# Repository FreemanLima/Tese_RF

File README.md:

Repo para manter coerente a organização dos ficheiros

Por agora a ideia é implementar e validar um transciever em PCB low cost para justificar fazer um mais xpto

Começando pela familia C1 da Texas

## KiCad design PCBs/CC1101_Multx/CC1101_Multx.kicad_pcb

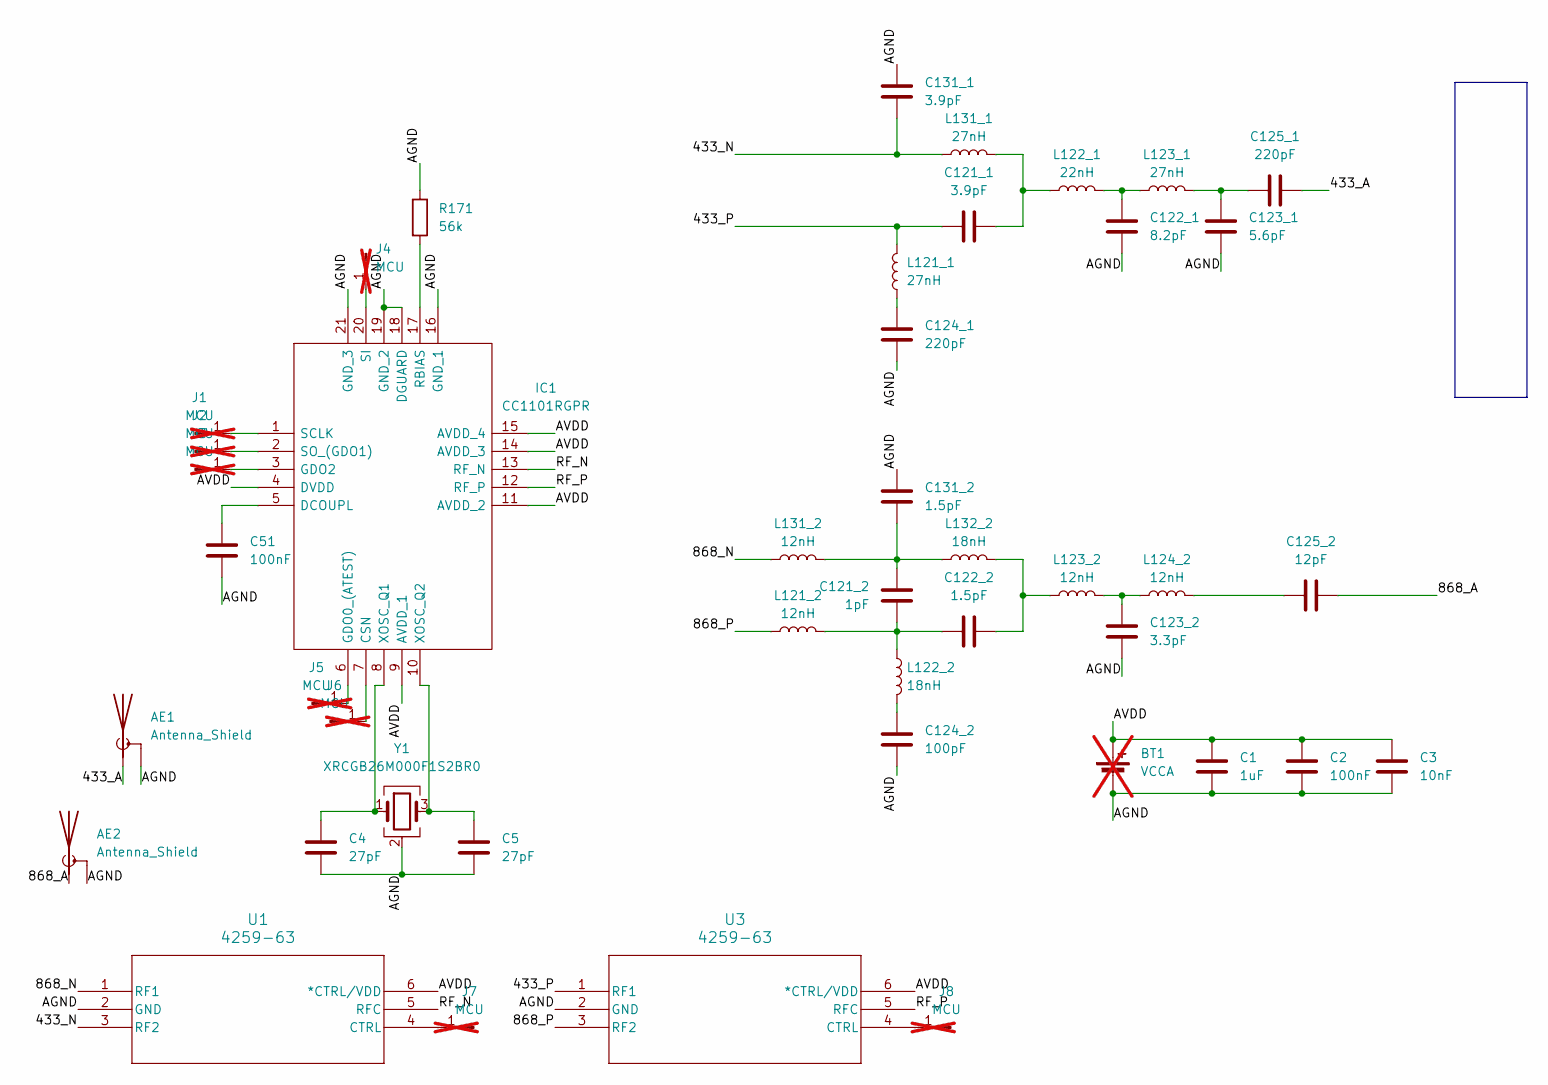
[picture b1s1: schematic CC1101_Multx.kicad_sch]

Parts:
AE1, AE2: Antenna_Shield; SMA_CONSMA020_062_G; Part Name CONSMA020.062-G; LCSC Part # C22467594
BT1: VCCA; PinHeader_1x02_P2.54mm_Vertical; not fitted
C1: 1uF; C_0603_1608Metric_Pad1.08x0.95mm_HandSolder; Part Name GRM155C71A105KE11J; LCSC Part # C126521
C2, C51: 100nF; C_0603_1608Metric_Pad1.08x0.95mm_HandSolder; Part Name GRM155C71H104JE19D; LCSC Part # C2189775
C3: 10nF; C_0603_1608Metric_Pad1.08x0.95mm_HandSolder; Part Name GRM155R71H103JA88D; LCSC Part # C162190
C4, C5: 27pF; C_0603_1608Metric_Pad1.08x0.95mm_HandSolder; Part Name GRM1555C1E270JA01D; LCSC Part # C710837
C121_1, C131_1: 3.9pF; C_0603_1608Metric_Pad1.08x0.95mm_HandSolder; Part Name GJM1555C1H3R9WB01D; LCSC Part # C88893
C121_2: 1pF; C_0603_1608Metric_Pad1.08x0.95mm_HandSolder; Part Name GCM1555C1H1R0JA16D; LCSC Part # C710646
C122_1: 8.2pF; C_0603_1608Metric_Pad1.08x0.95mm_HandSolder; Part Name GCQ1555C1H8R2WB01D; LCSC Part # C2272083
C122_2, C131_2: 1.5pF; C_0603_1608Metric_Pad1.08x0.95mm_HandSolder; Part Name GCM1555C1H1R5JA16D; LCSC Part # C710647
C123_1: 5.6pF; C_0603_1608Metric_Pad1.08x0.95mm_HandSolder; Part Name GJM1555C1H5R6BB01D; LCSC Part # C161329
C123_2: 3.3pF; C_0603_1608Metric_Pad1.08x0.95mm_HandSolder; Part Name GJM1555C1H3R3BB01D; LCSC Part # C76906
C124_1, C125_1: 220pF; C_0603_1608Metric_Pad1.08x0.95mm_HandSolder; Part Name GCM1555C1H221JA16D; LCSC Part # C126503
C124_2: 100pF; C_0603_1608Metric_Pad1.08x0.95mm_HandSolder; Part Name GCM1555C1H101FA16D; LCSC Part # C2941926
C125_2: 12pF; C_0603_1608Metric_Pad1.08x0.95mm_HandSolder; Part Name GRM1555C1H120JA01D; LCSC Part # C76948
IC1: CC1101RGPR; QFN50P400X400X100-21N-D; Mouser Part Number 595-CC1101RGPR
J1, J2, J3, J4, J5, J6, J7, J8: MCU; PinHeader_1x01_P2.54mm_Vertical; not fitted
L121_1, L123_1, L131_1: 27nH; L_0603_1608Metric; Part Name LQW15AN27NJ8ZD; LCSC Part # C2043861
L121_2, L123_2, L131_2: 12nH; L_0603_1608Metric; Part Name LQW15AN12NJ80D; LCSC Part # C2986278
L122_1: 22nH; L_0603_1608Metric; Part Name LQW15AN22NG8ZD; LCSC Part # C2044066
L122_2, L132_2: 18nH; L_0603_1608Metric; Part Name LQW15AN18NJ8ZD; LCSC Part # C437365
L124_2: 12nH; L_0603_1608Metric; Part Name LQW18AN12NG00D; LCSC Part # C98068
R171: 56k; R_0603_1608Metric_Pad0.98x0.95mm_HandSolder; Part Name ERJ-PA2F5602X; LCSC Part # C427251
U1, U3: 4259-63; SC-70-6_PSM-M; Part Name 4259-63; Digikey Part # 1046-1011-1-ND
Y1: XRCGB26M000F1S2BR0; Crystal_SMD_SeikoEpson_FA128-4Pin_2.0x1.6mm; Part Name XRCGB26M000F1S2BR0; LCSC Part # C7129840

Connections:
/433_A: AE1.1 (A), C125_1.1
/433_N: C131_1.1, L131_1.1, U1.3 (RF2)
/433_P: C121_1.1, L121_1.2, U3.1 (RF1)
/868_A: AE2.1 (A), C125_2.1
/868_N: L131_2.1, U1.1 (RF1)
/868_P: L121_2.1, U3.3 (RF2)
/AGND: AE1.2 (Shield), AE2.2 (Shield), BT1.2 (-), C1.1, C2.1, C3.1, C4.1, C5.1, C51.2, C122_1.1, C123_1.1, C123_2.1, C124_1.1, C124_2.1, C131_1.2, C131_2.2, IC1.16 (GND_1), IC1.18 (DGUARD), IC1.19 (GND_2), IC1.21 (GND_3), R171.1, U1.2 (GND), U3.2 (GND), Y1.2 (G), Y1.4 (G); also elsewhere on the board
/AVDD: BT1.1 (+), C1.2, C2.2, C3.2, IC1.4 (DVDD), IC1.9 (AVDD_1), IC1.11 (AVDD_2), IC1.14 (AVDD_3), IC1.15 (AVDD_4), U1.6 (*CTRL/VDD), U3.6 (*CTRL/VDD)
/RF_N: IC1.13 (RF_N), U1.5 (RFC)
/RF_P: IC1.12 (RF_P), U3.5 (RFC)
unnamed: C121_1.2, L122_1.1, L131_1.2
unnamed: C121_2.1, C131_2.1, L131_2.2, L132_2.1
unnamed: C121_2.2, C122_2.1, L121_2.2, L122_2.1
unnamed: C122_1.2, L122_1.2, L123_1.1
unnamed: C122_2.2, L123_2.1, L132_2.2
unnamed: C123_1.2, C125_1.2, L123_1.2
unnamed: C123_2.2, L123_2.2, L124_2.1
unnamed: C124_1.2, L121_1.1
unnamed: C124_2.2, L122_2.2
unnamed: C125_2.2, L124_2.2
unnamed: IC1.7 (CSN), J6.1 (Pin_1_1)
unnamed: C51.1, IC1.5 (DCOUPL)
unnamed: IC1.6 (GDO0_(ATEST)), J5.1 (Pin_1_1)
unnamed: IC1.3 (GDO2), J3.1 (Pin_1_1)
unnamed: IC1.17 (RBIAS), R171.2
unnamed: IC1.1 (SCLK), J1.1 (Pin_1_1)
unnamed: IC1.20 (SI), J4.1 (Pin_1_1)
unnamed: IC1.2 (SO_(GDO1)), J2.1 (Pin_1_1)
unnamed: C4.2, IC1.8 (XOSC_Q1), Y1.1
unnamed: C5.2, IC1.10 (XOSC_Q2), Y1.3
unnamed: J7.1 (Pin_1_1), U1.4 (CTRL)
unnamed: J8.1 (Pin_1_1), U3.4 (CTRL)

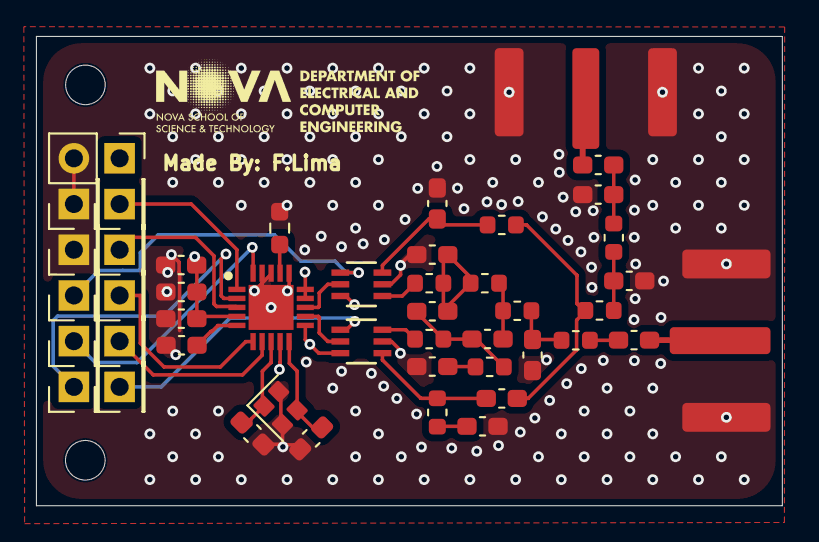
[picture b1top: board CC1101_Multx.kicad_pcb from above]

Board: 4 copper layers, 41.4 x 26.1 mm, 46 parts (0 on the bottom side), 32 nets.

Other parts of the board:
J1#2, J9: MCU; PinHeader_1x01_P2.54mm_Vertical

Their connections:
/AGND: J1#2.1 (Pin_1_1), J9.1 (Pin_1_1); also elsewhere on the board

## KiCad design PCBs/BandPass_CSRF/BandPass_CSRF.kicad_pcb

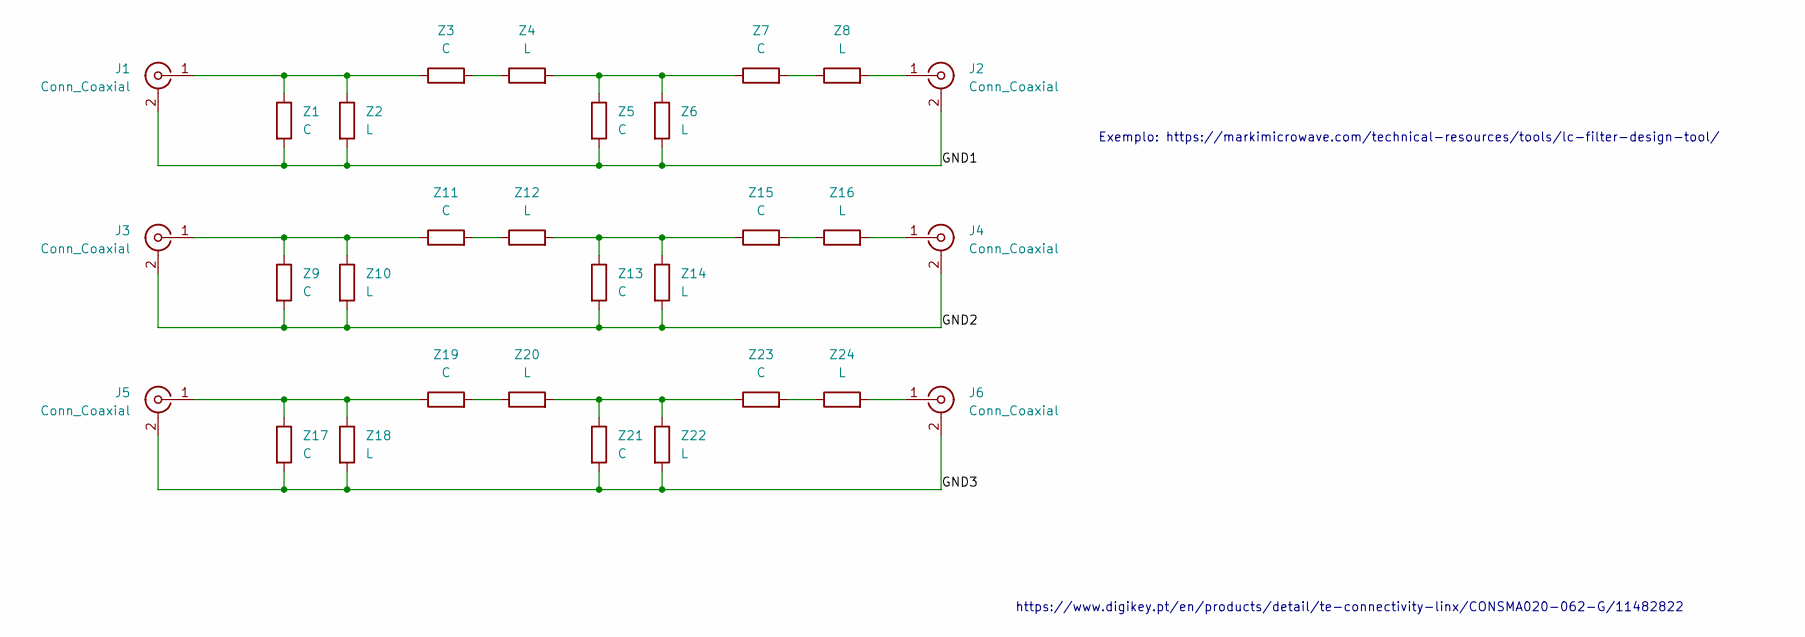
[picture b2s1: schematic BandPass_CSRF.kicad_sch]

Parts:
J1, J2, J3, J4, J5, J6: Conn_Coaxial; SMA_CONSMA020_062_G
Z1, Z3, Z5, Z7, Z9, Z11, Z13, Z15, Z17, Z19, Z21, Z23: C; C_0805_2012Metric_Pad1.18x1.45mm_HandSolder
Z2, Z4, Z6, Z8, Z10, Z12, Z14, Z16, Z18, Z20, Z22, Z24: L; C_0805_2012Metric_Pad1.18x1.45mm_HandSolder

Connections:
/GND1: J1.2 (Ext), J2.2 (Ext), Z1.2, Z2.2, Z5.2, Z6.2
/GND2: J3.2 (Ext), J4.2 (Ext), Z9.2, Z10.2, Z13.2, Z14.2
/GND3: J5.2 (Ext), J6.2 (Ext), Z17.2, Z18.2, Z21.2, Z22.2
unnamed: J1.1 (In), Z1.1, Z2.1, Z3.1
unnamed: J2.1 (In), Z8.2
unnamed: J3.1 (In), Z9.1, Z10.1, Z11.1
unnamed: J4.1 (In), Z16.2
unnamed: J5.1 (In), Z17.1, Z18.1, Z19.1
unnamed: J6.1 (In), Z24.2
unnamed: Z3.2, Z4.1
unnamed: Z4.2, Z5.1, Z6.1, Z7.1
unnamed: Z7.2, Z8.1
unnamed: Z11.2, Z12.1
unnamed: Z12.2, Z13.1, Z14.1, Z15.1
unnamed: Z15.2, Z16.1
unnamed: Z19.2, Z20.1
unnamed: Z20.2, Z21.1, Z22.1, Z23.1
unnamed: Z23.2, Z24.1

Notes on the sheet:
Exemplo: https://markimicrowave.com/technical-resources/tools/lc-filter-design-tool/
https://www.digikey.pt/en/products/detail/te-connectivity-linx/CONSMA020-062-G/11482822

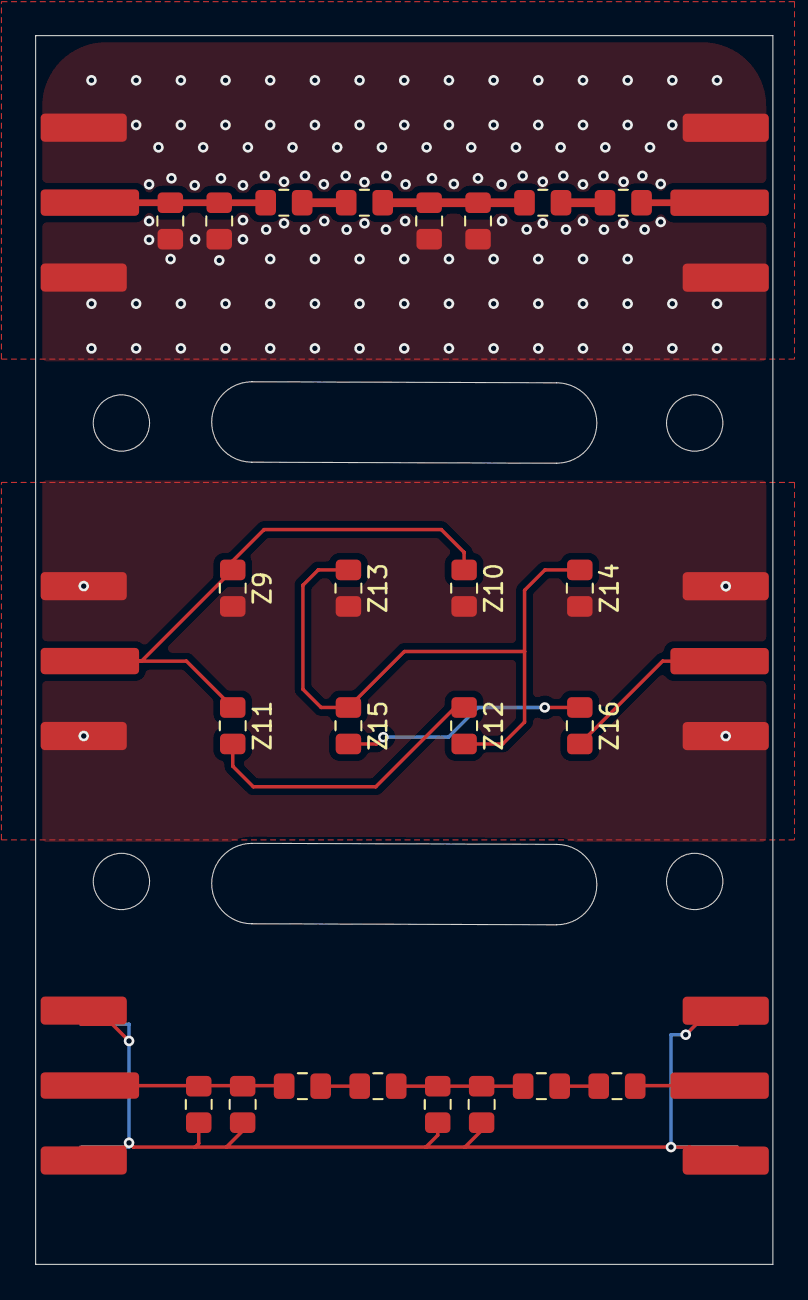
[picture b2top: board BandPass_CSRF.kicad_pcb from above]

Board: 2 copper layers, 41.9 x 69.9 mm, 30 parts (0 on the bottom side), 18 nets.

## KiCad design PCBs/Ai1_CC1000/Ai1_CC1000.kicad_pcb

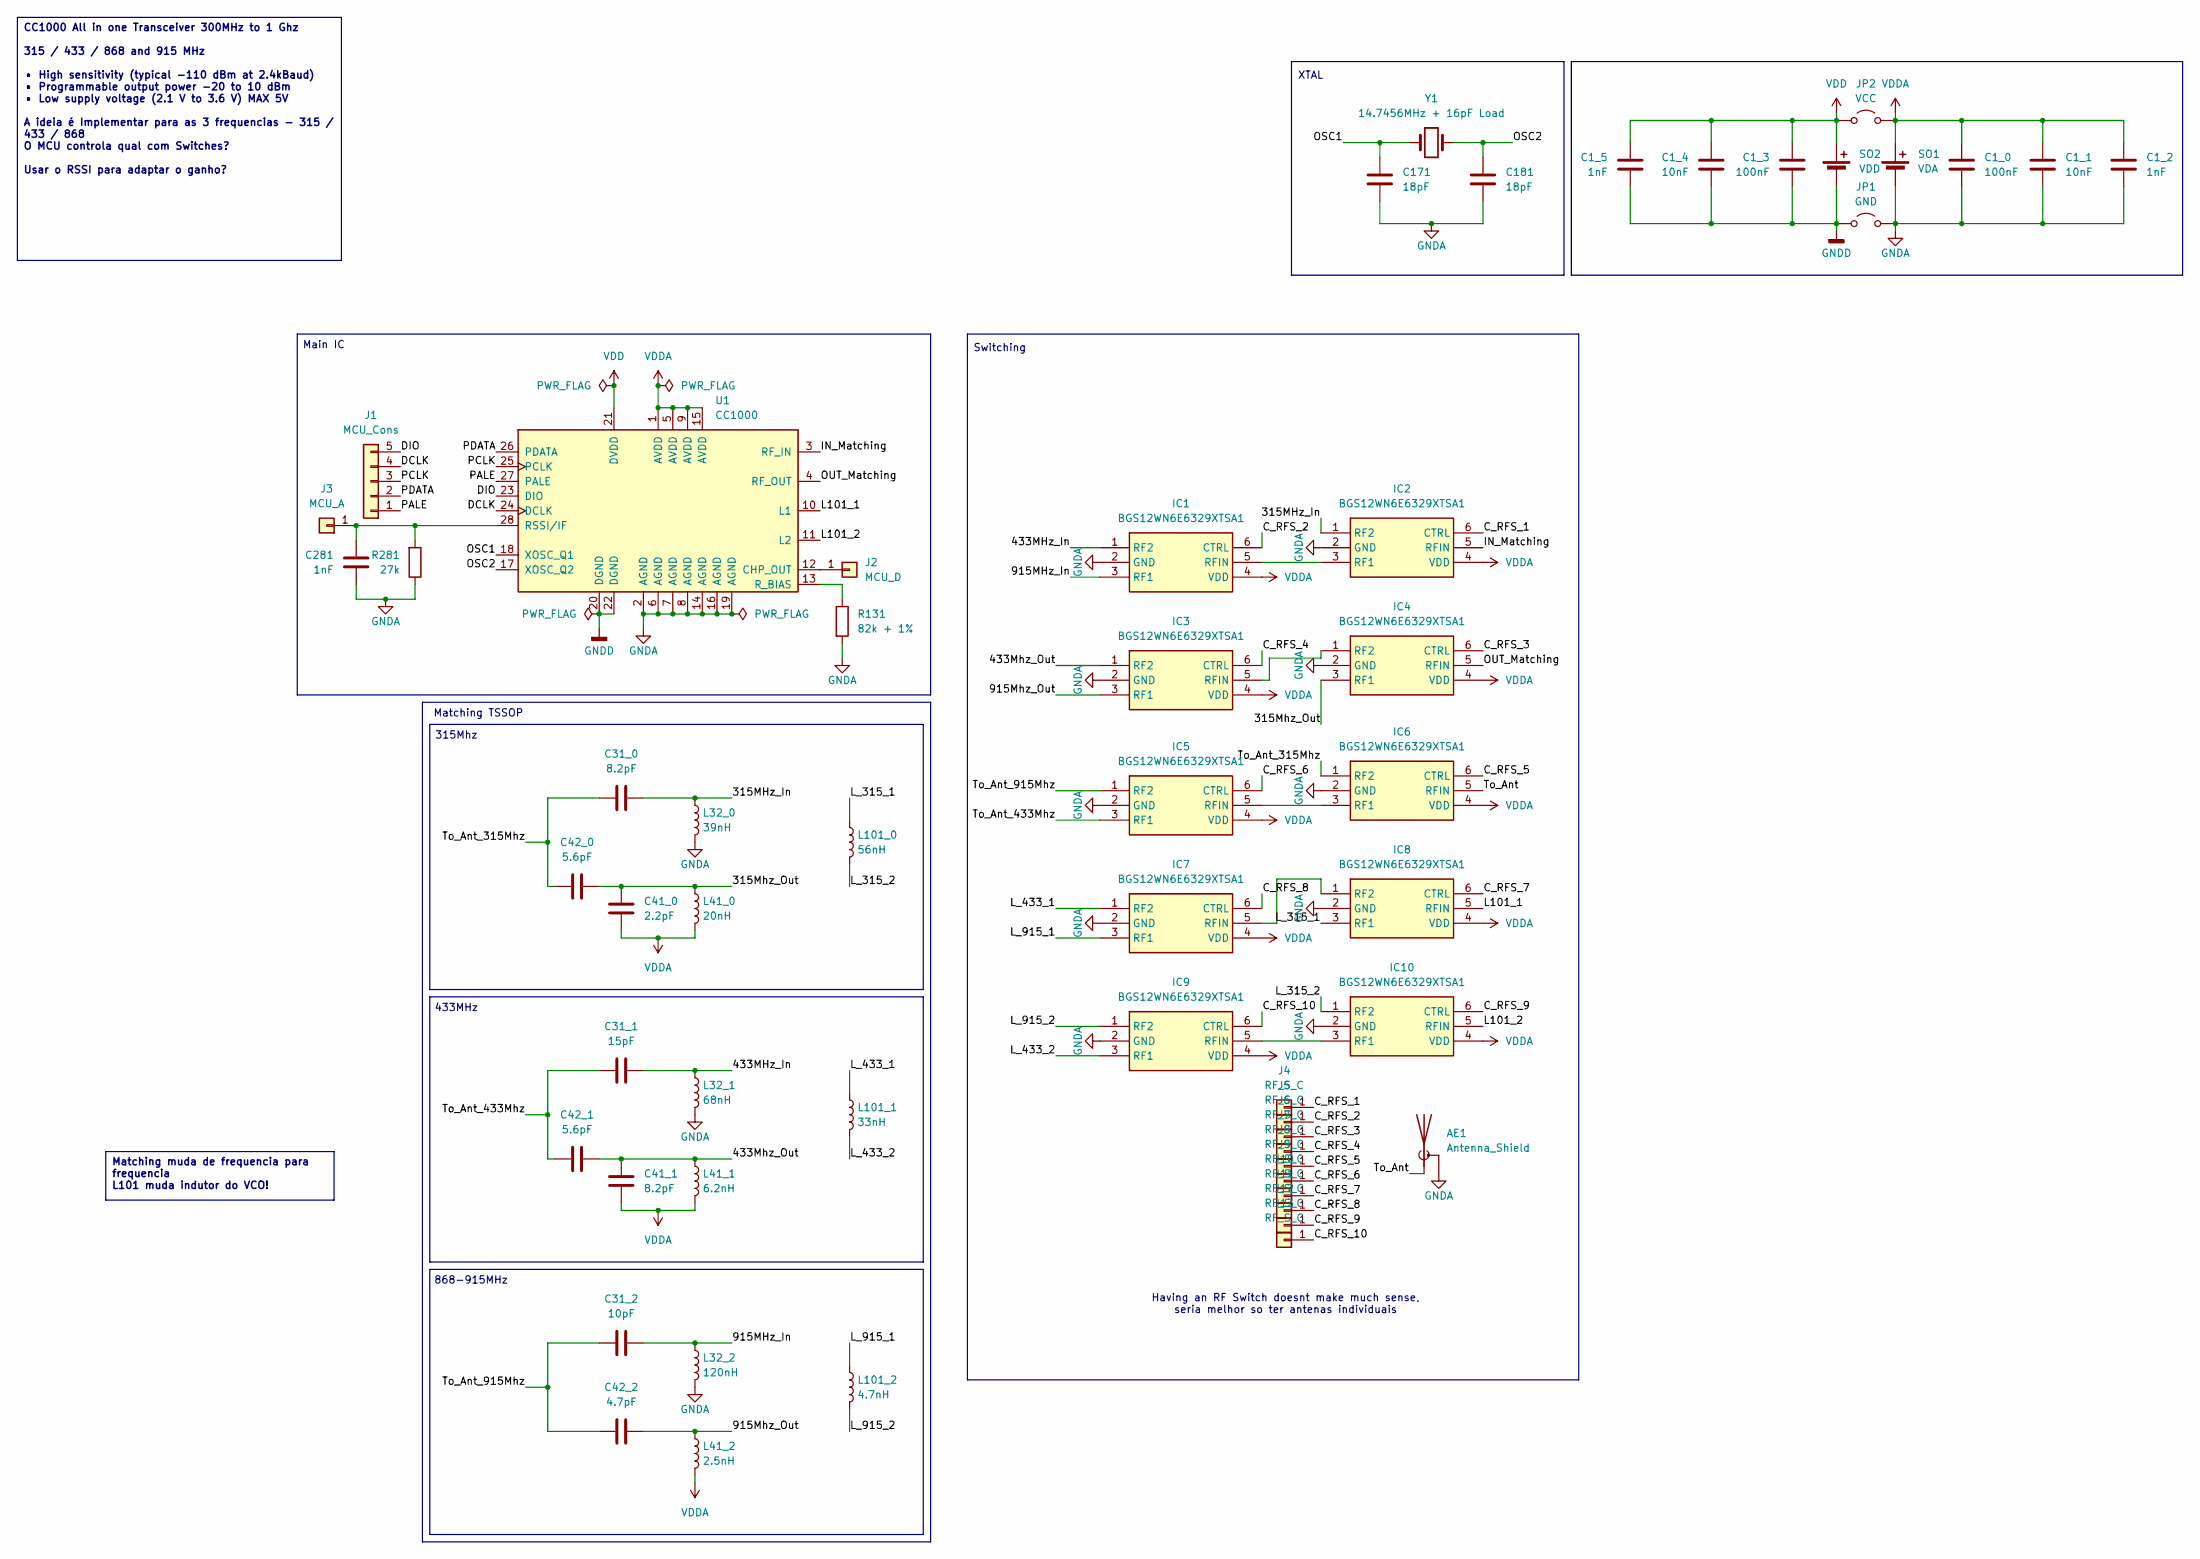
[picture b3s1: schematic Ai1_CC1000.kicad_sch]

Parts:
AE1: Antenna_Shield; SMA_Molex_73251-1153_EdgeMount_Horizontal
C1_0, C1_3: 100nF; C_0603_1608Metric
C1_1, C1_4: 10nF; C_0603_1608Metric
C1_2, C1_5, C281: 1nF; C_0603_1608Metric
C31_0, C41_1: 8.2pF; C_0603_1608Metric
C31_1: 15pF; C_0603_1608Metric
C31_2: 10pF; C_0603_1608Metric
C41_0: 2.2pF; C_0603_1608Metric
C42_0, C42_1: 5.6pF; C_0603_1608Metric
C42_2: 4.7pF; C_0603_1608Metric
C171, C181: 18pF; C_0603_1608Metric
IC1, IC2, IC3, IC4, IC5, IC6, IC7, IC8, IC9, IC10: BGS12WN6E6329XTSA1; Infineon_PG-TSNP-6-10_0.7x1.1mm_0.7x1.1mm_P0.4mm; Mouser Part Number 726-BGS12WN6E6329XTS
J1: MCU_Cons; PinSocket_1x05_P2.54mm_Vertical
J2: MCU_D; PinSocket_1x01_P2.54mm_Vertical
J3: MCU_A; PinSocket_1x01_P2.54mm_Vertical
J4, J5, J6, J7, J8, J9, J10, J11, J12, J13: RF_S_C; PinSocket_1x01_P2.54mm_Vertical
JP1: GND; SolderJumper-2_P1.3mm_Open_TrianglePad1.0x1.5mm
JP2: VCC; SolderJumper-2_P1.3mm_Open_TrianglePad1.0x1.5mm
L32_0: 39nH; C_0805_2012Metric
L32_1: 68nH; C_0805_2012Metric
L32_2: 120nH; C_0805_2012Metric
L41_0: 20nH; C_0805_2012Metric
L41_1: 6.2nH; C_0805_2012Metric
L41_2: 2.5nH; C_0805_2012Metric
L101_0: 56nH; C_0805_2012Metric
L101_1: 33nH; C_0805_2012Metric
L101_2: 4.7nH; C_0805_2012Metric
R131: 82k + 1%; R_0603_1608Metric
R281: 27k; R_0603_1608Metric
SO1: VDA; TerminalBlock_Phoenix_MPT-0,5-2-2.54_1x02_P2.54mm_Horizontal
SO2: VDD; TerminalBlock_Phoenix_MPT-0,5-2-2.54_1x02_P2.54mm_Horizontal
U1: CC1000; TSSOP-28_4.4x9.7mm_P0.65mm
Y1: 14.7456MHz + 16pF Load; Crystal_SMD_HC49-SD_HandSoldering

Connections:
/315MHz_In: C31_0.2, IC2.1 (RF2), L32_0.1
/315Mhz_Out: C41_0.2, C42_0.2, IC4.3 (RF1), L41_0.1
/433MHz_In: C31_1.2, IC1.1 (RF2), L32_1.1
/433Mhz_Out: C41_1.2, C42_1.2, IC3.1 (RF2), L41_1.1
/915MHz_In: C31_2.2, IC1.3 (RF1), L32_2.1
/915Mhz_Out: C42_2.2, IC3.3 (RF1), L41_2.1
/C_RFS_1: IC2.6 (CTRL), J4.1 (Pin_1_1)
/C_RFS_2: IC1.6 (CTRL), J5.1 (Pin_1_1)
/C_RFS_3: IC4.6 (CTRL), J6.1 (Pin_1_1)
/C_RFS_4: IC3.6 (CTRL), J7.1 (Pin_1_1)
/C_RFS_5: IC6.6 (CTRL), J8.1 (Pin_1_1)
/C_RFS_6: IC5.6 (CTRL), J9.1 (Pin_1_1)
/C_RFS_7: IC8.6 (CTRL), J10.1 (Pin_1_1)
/C_RFS_8: IC7.6 (CTRL), J11.1 (Pin_1_1)
/C_RFS_9: IC10.6 (CTRL), J12.1 (Pin_1_1)
/C_RFS_10: IC9.6 (CTRL), J13.1 (Pin_1_1)
/DCLK: J1.4, U1.24 (DCLK)
/DIO: J1.5, U1.23 (DIO)
/IN_Matching: IC2.5 (RFIN), U1.3 (RF_IN)
/L101_1: IC8.5 (RFIN), U1.10 (L1)
/L101_2: IC10.5 (RFIN), U1.11 (L2)
/L_315_1: IC8.3 (RF1), L101_0.1
/L_315_2: IC10.1 (RF2), L101_0.2
/L_433_1: IC7.1 (RF2), L101_1.1
/L_433_2: IC9.3 (RF1), L101_1.2
/L_915_1: IC7.3 (RF1), L101_2.1
/L_915_2: IC9.1 (RF2), L101_2.2
/OSC1: C171.1, U1.18 (XOSC_Q1), Y1.1
/OSC2: C181.1, U1.17 (XOSC_Q2), Y1.2
/OUT_Matching: IC4.5 (RFIN), U1.4 (RF_OUT)
/PALE: J1.1, U1.27 (PALE)
/PCLK: J1.3, U1.25 (PCLK)
/PDATA: J1.2, U1.26 (PDATA)
/To_Ant: AE1.1 (A), IC6.5 (RFIN)
/To_Ant_315Mhz: C31_0.1, C42_0.1, IC6.1 (RF2)
/To_Ant_433Mhz: C31_1.1, C42_1.1, IC5.3 (RF1)
/To_Ant_915Mhz: C31_2.1, C42_2.1, IC5.1 (RF2)
GNDA: AE1.2 (Shield), C1_0.1, C1_1.1, C1_2.1, C171.2, C181.2, C281.2, IC1.2 (GND), IC2.2 (GND), IC3.2 (GND), IC4.2 (GND), IC5.2 (GND), IC6.2 (GND), IC7.2 (GND), IC8.2 (GND), IC9.2 (GND), IC10.2 (GND), JP1.2 (B), L32_0.2, L32_1.2, L32_2.2, R131.2, R281.1, SO1.2 (-), U1.2 (AGND), U1.6 (AGND), U1.7 (AGND), U1.8 (AGND), U1.14 (AGND), U1.16 (AGND), U1.19 (AGND)
GNDD: C1_3.1, C1_4.1, C1_5.1, JP1.1 (A), SO2.2 (-), U1.20 (DGND), U1.22 (DGND)
unnamed: IC1.5 (RFIN), IC2.3 (RF1)
unnamed: IC3.5 (RFIN), IC4.1 (RF2)
unnamed: IC5.5 (RFIN), IC6.3 (RF1)
unnamed: IC7.5 (RFIN), IC8.1 (RF2)
unnamed: IC9.5 (RFIN), IC10.3 (RF1)
unnamed: J2.1 (Pin_1_1), U1.12 (CHP_OUT)
unnamed: C281.1, J3.1 (Pin_1_1), R281.2, U1.28 (RSSI/IF)
unnamed: R131.1, U1.13 (R_BIAS)
VDD: C1_3.2, C1_4.2, C1_5.2, JP2.1 (A), SO2.1 (+), U1.21 (DVDD)
VDDA: C1_0.2, C1_1.2, C1_2.2, C41_0.1, C41_1.1, IC1.4 (VDD), IC2.4 (VDD), IC3.4 (VDD), IC4.4 (VDD), IC5.4 (VDD), IC6.4 (VDD), IC7.4 (VDD), IC8.4 (VDD), IC9.4 (VDD), IC10.4 (VDD), JP2.2 (B), L41_0.2, L41_1.2, L41_2.2, SO1.1 (+), U1.1 (AVDD), U1.5 (AVDD), U1.9 (AVDD), U1.15 (AVDD)

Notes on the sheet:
Matching TSSOP
868-915MHz
433MHz
Switching
Having an RF Switch doesnt make much sense, seria melhor so ter antenas individuais
315Mhz
Main IC
XTAL
CC1000 All in one Transceiver 300MHz to 1 Ghz 315 / 433 / 868 and 915 MHz • High sensitivity (typical -110 dBm at 2.4kBaud) • Programmable output power -20 to 10 dBm • Low supply voltage (2.1 V to 3.6 V) MAX 5V A ideia é Implementar para as 3 frequencias - 315 / 433 / 868 O MCU controla qual com Sw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
Matching muda de frequencia para frequencia L101 muda indutor do VCO!

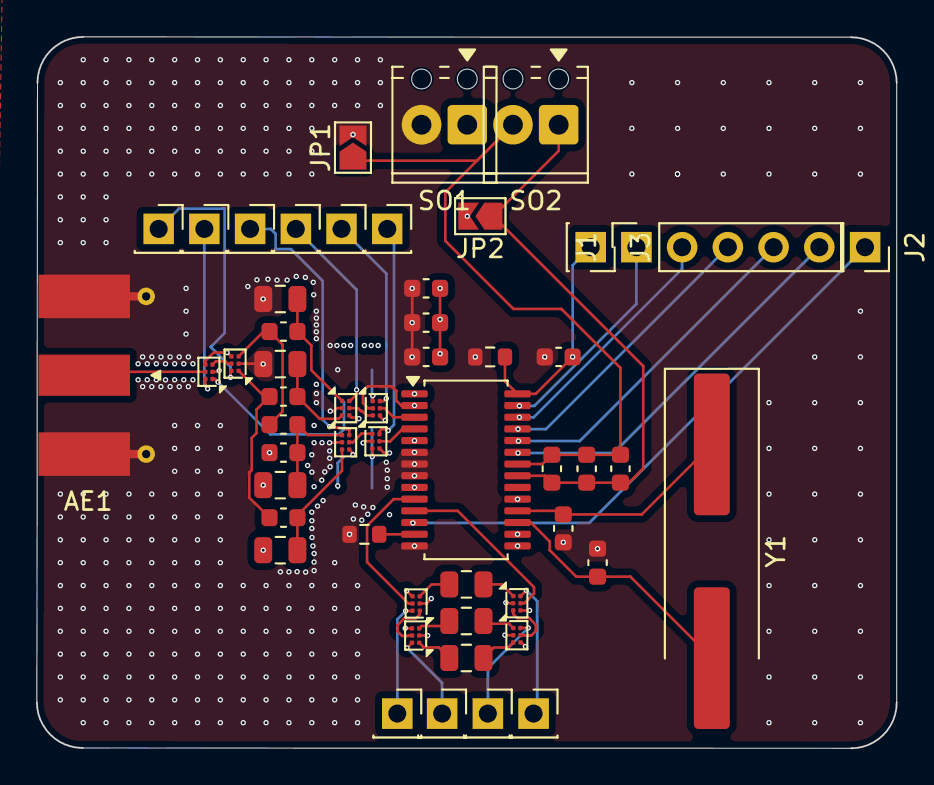
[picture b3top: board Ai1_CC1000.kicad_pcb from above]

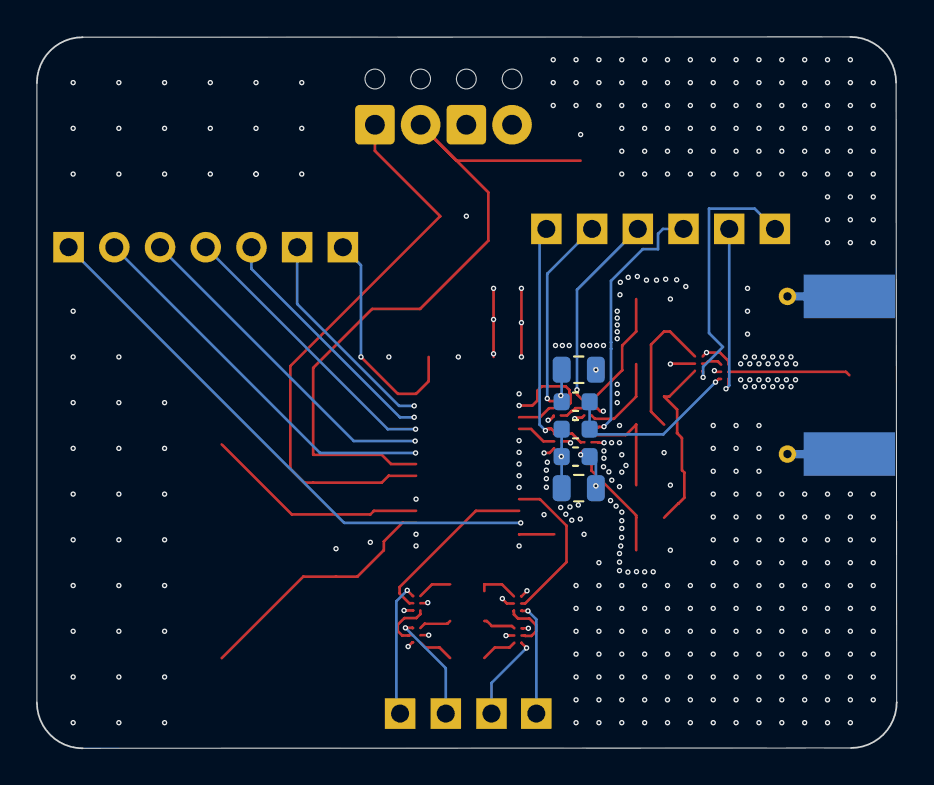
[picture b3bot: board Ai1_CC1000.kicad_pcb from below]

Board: 4 copper layers, 47.8 x 39.5 mm, 58 parts (5 on the bottom side), 49 nets.

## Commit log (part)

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2026-06-18 Para meter no git
2026-06-18 gitting
2026-06-18 Gitte
    Updated project description and added initial goals.
2026-06-19 Switching1
    Falta os switches das bobinas
2026-06-19 gitignore
2026-06-19 Com L switchs
2026-06-19 PDF_V1
2026-06-19 DRC LIMPO E SWITCH L101
2026-06-19 Crystal Escolhido
2026-06-19 V2_sche
2026-06-22 innit layout
2026-06-22 deeesignhelp
2026-06-22 book
    page 307 ou 595
2026-06-23 ltspice
2026-06-23 grail
2026-06-24 papersmatching
2026-06-24 paper
2026-06-25 innit scripts
2026-06-26 scripst3
2026-06-26 Layout V2
2026-06-26 Layout V3 Antena needs attention
    To check with prof
    Antenas? Multiple?
2026-06-27 PCB ready for fab 1 ?
    Problemas atuais, antena e uma revisao sobre os traces, mas de acordo com a calculador de microstrip nenhum trace tem mais q 15EL ou seja menos de /4 entao nao devem desviar o matching
2026-06-27 gerbers
2026-06-30 dump
2026-06-30 CC1101 Innit
    A esquematica ta feita toda ja :)
2026-06-30 Layout V1
